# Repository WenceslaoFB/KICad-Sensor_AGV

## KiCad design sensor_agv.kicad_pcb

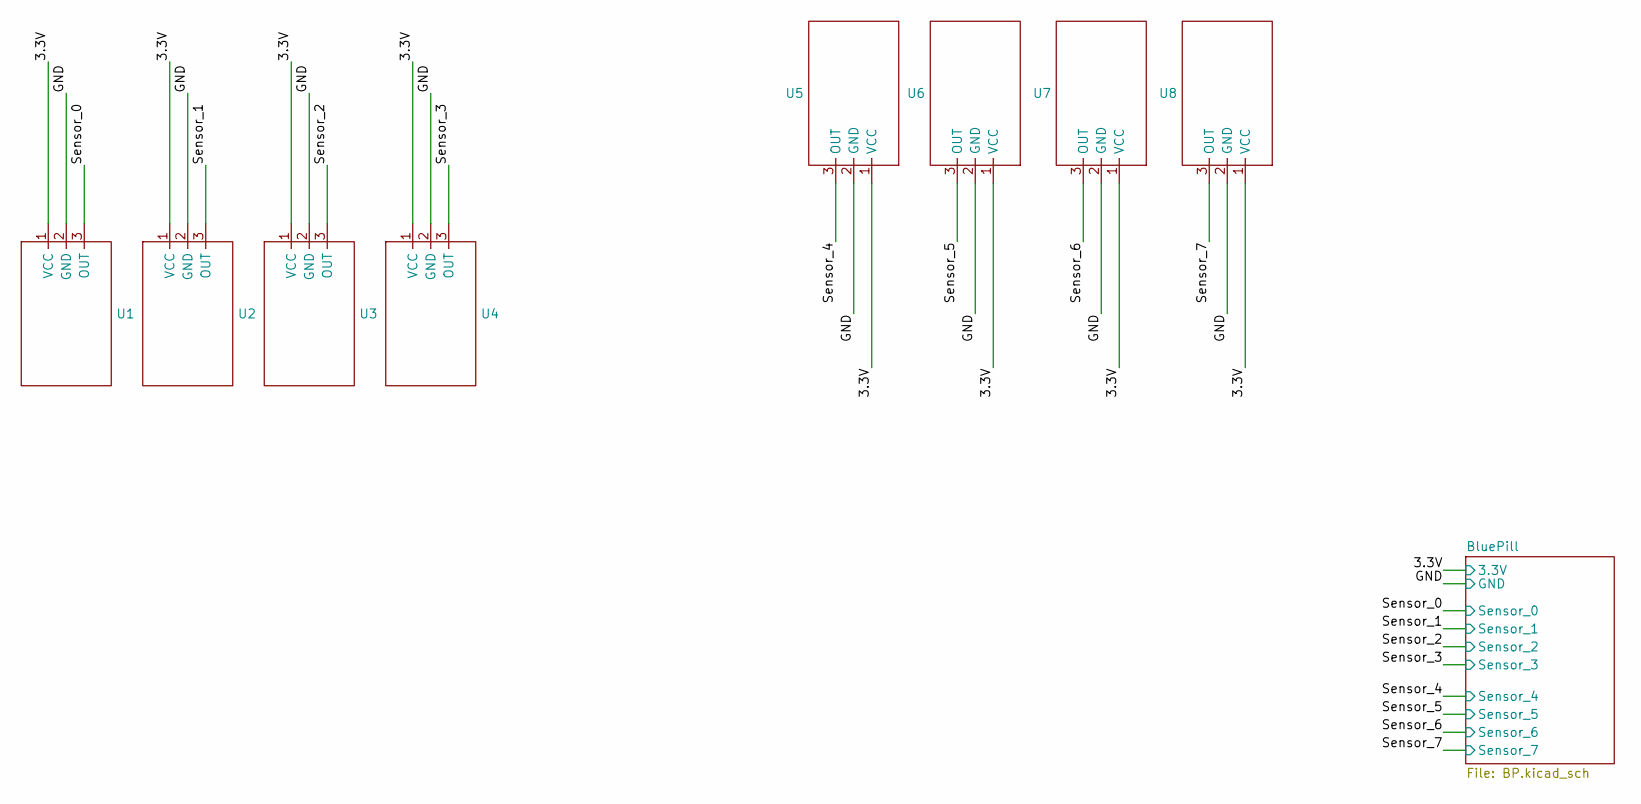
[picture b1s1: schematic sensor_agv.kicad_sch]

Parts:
U1, U2, U3, U4, U5, U6, U7, U8: PinHeader_1x03_P2.54mm_Vertical

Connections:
/3.3V: U1.1 (VCC), U2.1 (VCC), U3.1 (VCC), U4.1 (VCC), U5.1 (VCC), U6.1 (VCC), U7.1 (VCC), U8.1 (VCC); also elsewhere on the board
/GND: U1.2 (GND), U2.2 (GND), U3.2 (GND), U4.2 (GND), U5.2 (GND), U6.2 (GND), U7.2 (GND), U8.2 (GND); also elsewhere on the board
/Sensor_0: U1.3 (OUT); also elsewhere on the board
/Sensor_1: U2.3 (OUT); also elsewhere on the board
/Sensor_2: U3.3 (OUT); also elsewhere on the board
/Sensor_4: U5.3 (OUT); also elsewhere on the board
/Sensor_5: U6.3 (OUT); also elsewhere on the board
/Sensor_6: U7.3 (OUT); also elsewhere on the board
/Sensor_7: U8.3 (OUT); also elsewhere on the board

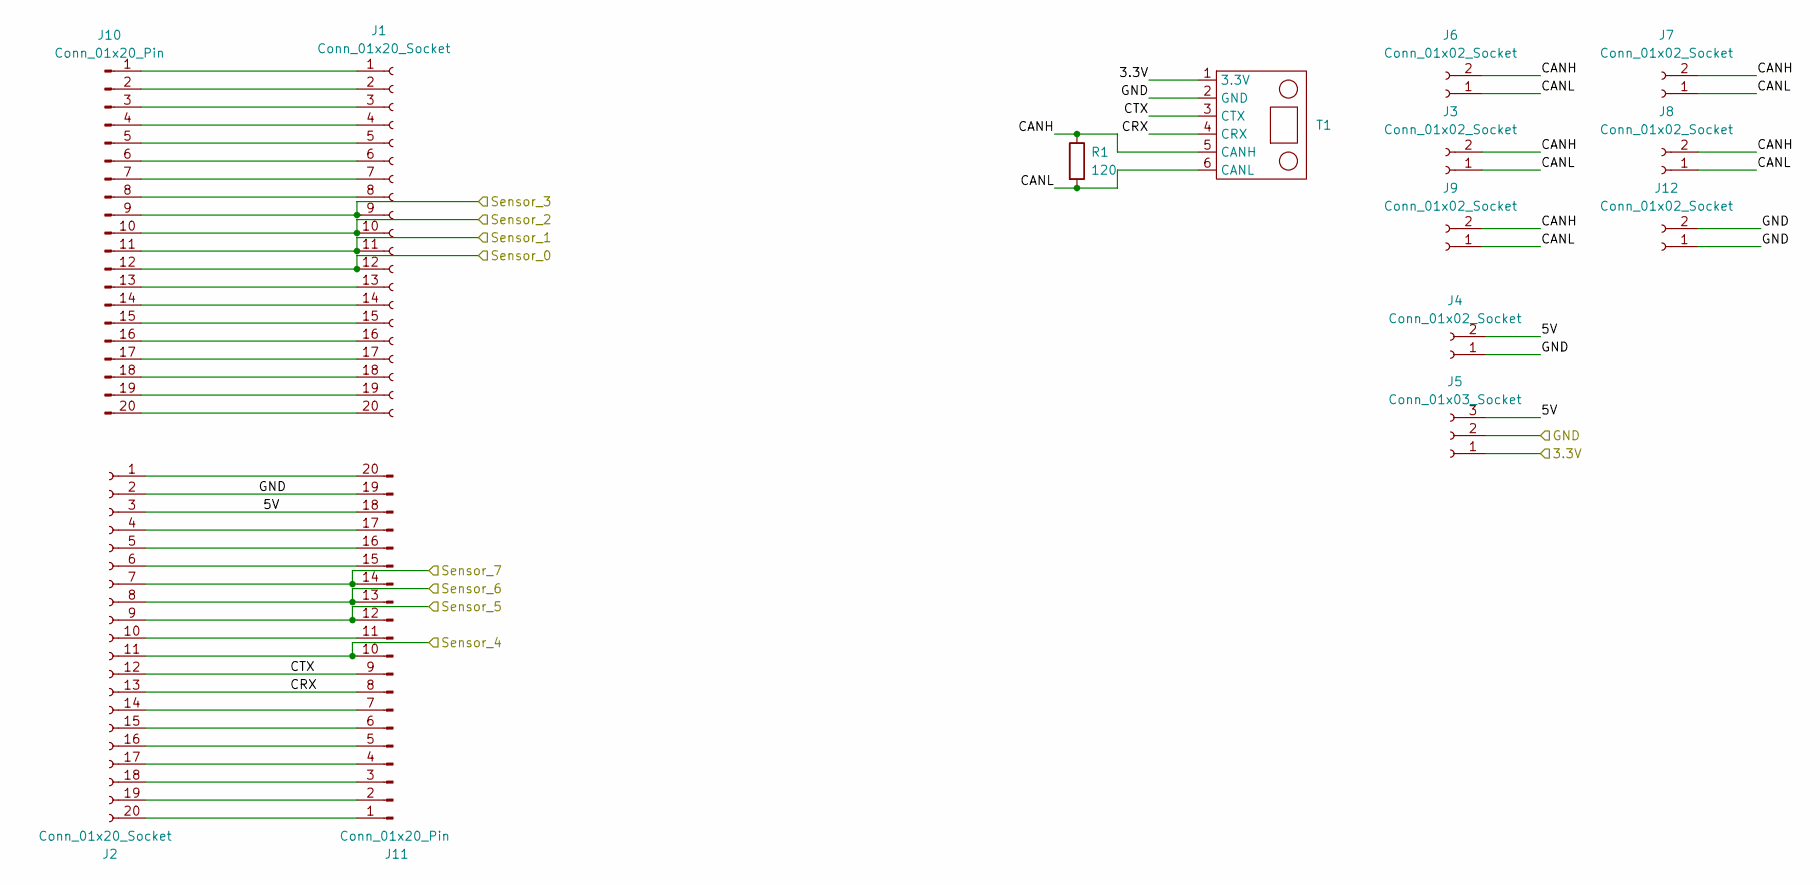
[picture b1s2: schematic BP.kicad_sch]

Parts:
J1, J2: Conn_01x20_Socket; PinSocket_1x20_P2.54mm_Vertical
J3, J4, J6, J7, J8, J9, J12: Conn_01x02_Socket; Conector_1x02
J5: Conn_01x03_Socket; PinSocket_1x03_P2.54mm_Vertical
J10, J11: Conn_01x20_Pin; PinHeader_1x20_P2.54mm_Vertical
R1: 120; R_Axial_DIN0204_L3.6mm_D1.6mm_P7.62mm_Horizontal
T1: PinSocket_1x06_P2.54mm_Vertical

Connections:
/3.3V: J5.1, T1.1 (3.3V); also elsewhere on the board
/BluePill/5V: J2.3, J4.2, J5.3, J11.18
/BluePill/CANH: J3.2, J6.2, J7.2, J8.2, J9.2, R1.1, T1.5 (CANH)
/BluePill/CANL: J3.1, J6.1, J7.1, J8.1, J9.1, R1.2, T1.6 (CANL)
/BluePill/CRX: J2.13, J11.8, T1.4 (CRX)
/BluePill/CTX: J2.12, J11.9, T1.3 (CTX)
/GND: J2.2, J4.1, J5.2, J11.19, J12.1, J12.2, T1.2 (GND); also elsewhere on the board
/Sensor_0: J1.12, J10.12; also elsewhere on the board
/Sensor_1: J1.11, J10.11; also elsewhere on the board
/Sensor_2: J1.10, J10.10; also elsewhere on the board
/Sensor_3: J1.9, J10.9
/Sensor_4: J2.11, J11.10; also elsewhere on the board
/Sensor_5: J2.9, J11.12; also elsewhere on the board
/Sensor_6: J2.8, J11.13; also elsewhere on the board
/Sensor_7: J2.7, J11.14; also elsewhere on the board
unnamed: J1.1, J10.1
unnamed: J1.2, J10.2
unnamed: J1.3, J10.3
unnamed: J1.4, J10.4
unnamed: J1.5, J10.5
unnamed: J1.6, J10.6
unnamed: J1.7, J10.7
unnamed: J1.8, J10.8
unnamed: J1.13, J10.13
unnamed: J1.14, J10.14
unnamed: J1.15, J10.15
unnamed: J1.16, J10.16
unnamed: J1.17, J10.17
unnamed: J1.18, J10.18
unnamed: J1.19, J10.19
unnamed: J1.20, J10.20
unnamed: J2.20, J11.1
unnamed: J2.19, J11.2
unnamed: J2.18, J11.3
unnamed: J2.17, J11.4
unnamed: J2.16, J11.5
unnamed: J2.15, J11.6
unnamed: J2.14, J11.7
unnamed: J2.10, J11.11
unnamed: J2.6, J11.15
unnamed: J2.5, J11.16
unnamed: J2.4, J11.17
unnamed: J2.1, J11.20

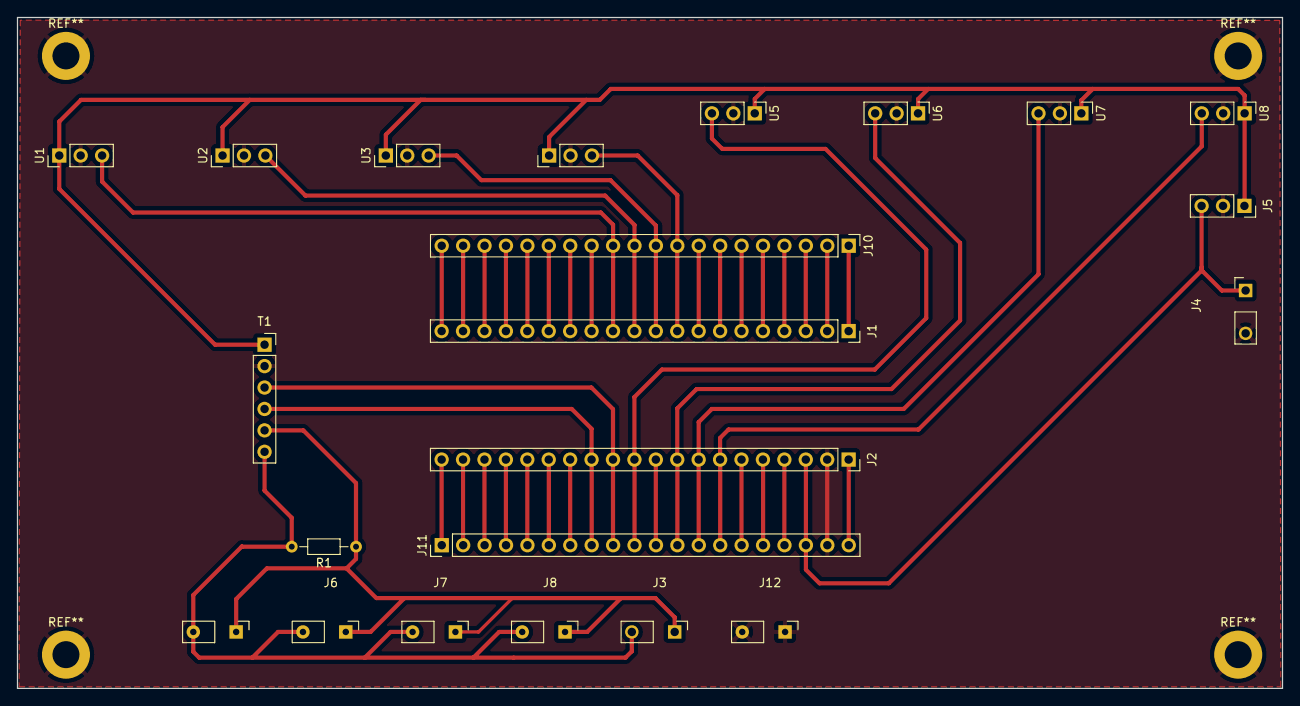
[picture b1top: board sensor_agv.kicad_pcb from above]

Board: 2 copper layers, 150.0 x 79.6 mm, 21 parts (0 on the bottom side), 43 nets.

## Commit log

2024-06-03 PCB casi terminada
